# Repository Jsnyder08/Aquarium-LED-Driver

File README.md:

# Reef-LED-Driver
3 Channel LED driver board with PWM fan control <br>
• Utilizes Meanwell LDD-H CC LED Drivers<br>
 Input 9-56 vdc<br>
 1000ma capable output<br>
• Features 3 channel design (Royal Blue, White/Lime, Violet/near IR)<br>
• Utilizes Meanwell SCW 12v DC/DC converter for Fan power<br>
 470ma max output current<br>
• Supports both PWM Fans (4pin) and Standard Fans (3pin)<br>

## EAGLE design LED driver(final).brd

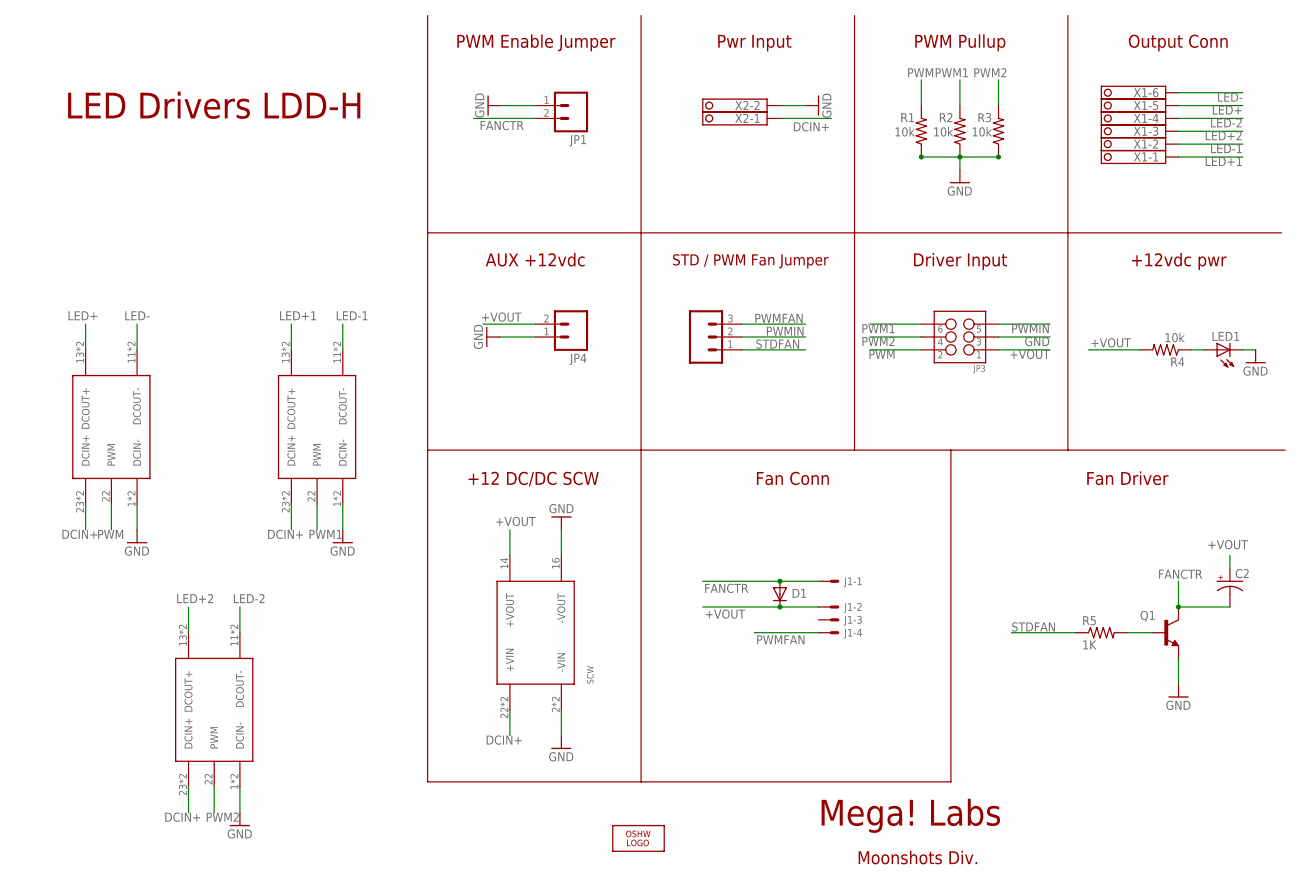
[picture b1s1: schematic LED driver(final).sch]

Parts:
C2: CPOL-USE3.5-8; E3,5-8
D1: CGRM4007-G; SOD-123_MINI-SMA
J1: 22-05-7048-04; 7395-04
JP1: M02LOCK; 1X02_LOCK
JP2: M03LOCK; 1X03_LOCK
JP3: M03X2SHROUD; 2X3-SHROUDED
JP4: M02-JST-2MM-SMT; JST-2-SMD
LED1: LEDCHIPLED_1206; CHIPLED_1206
LOGO2: OSHW_LOGO_6MILX0150-NT; OSHW_6X150_NOTEXT
Q1: BC808-NPN-SOT23-BEC; SOT23-BEC
R1, R2, R3, R4: 10k; M1206
R5: 1K; M1206
U$1, U$2, U$3: LDD_H
U$5: SCW
X1: 1751280
X2: 1751248

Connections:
+VOUT: C2.+, D1.C, J1.2, JP3.1, JP4.2 (1), R4.2, U$5.14 (+VOUT)
C: Q1.B, R5.2
DCIN+: U$1.23 (DCIN+), U$1.24 (DCIN+), U$2.23 (DCIN+), U$2.24 (DCIN+), U$3.23 (DCIN+), U$3.24 (DCIN+), U$5.22 (+VIN), U$5.23 (+VIN), X2.1
FANCTR: C2.-, D1.A, J1.1, JP1.2, Q1.C
GND: JP1.1, JP3.3, JP4.1 (2), LED1.C, Q1.E, R1.1, R2.1, R3.1, U$1.1 (DCIN-), U$1.2 (DCIN-), U$2.1 (DCIN-), U$2.2 (DCIN-), U$3.1 (DCIN-), U$3.2 (DCIN-), U$5.2 (-VIN), U$5.3 (-VIN), U$5.16 (-VOUT), X2.2
LED+: U$1.13 (DCOUT+), U$1.14 (DCOUT+), X1.5
LED+1: U$2.13 (DCOUT+), U$2.14 (DCOUT+), X1.1
LED+2: U$3.13 (DCOUT+), U$3.14 (DCOUT+), X1.3
LED-: U$1.11 (DCOUT-), U$1.12 (DCOUT-), X1.6
LED-1: U$2.11 (DCOUT-), U$2.12 (DCOUT-), X1.2
LED-2: U$3.11 (DCOUT-), U$3.12 (DCOUT-), X1.4
unnamed: LED1.A, R4.1
PWM: JP3.2, R1.2, U$1.22 (PWM)
PWM1: JP3.6, R2.2, U$2.22 (PWM)
PWM2: JP3.4, R3.2, U$3.22 (PWM)
PWMFAN: J1.4, JP2.3
PWMIN: JP2.2, JP3.5
STDFAN: JP2.1, R5.1

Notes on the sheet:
Output Conn
+12vdc pwr
Fan Driver
PWM Pullup
Driver Input
Pwr Input
STD / PWM Fan Jumper
AUX +12vdc
PWM Enable Jumper
Fan Conn
+12 DC/DC SCW
LED Drivers LDD-H
Mega! Labs
Moonshots Div.

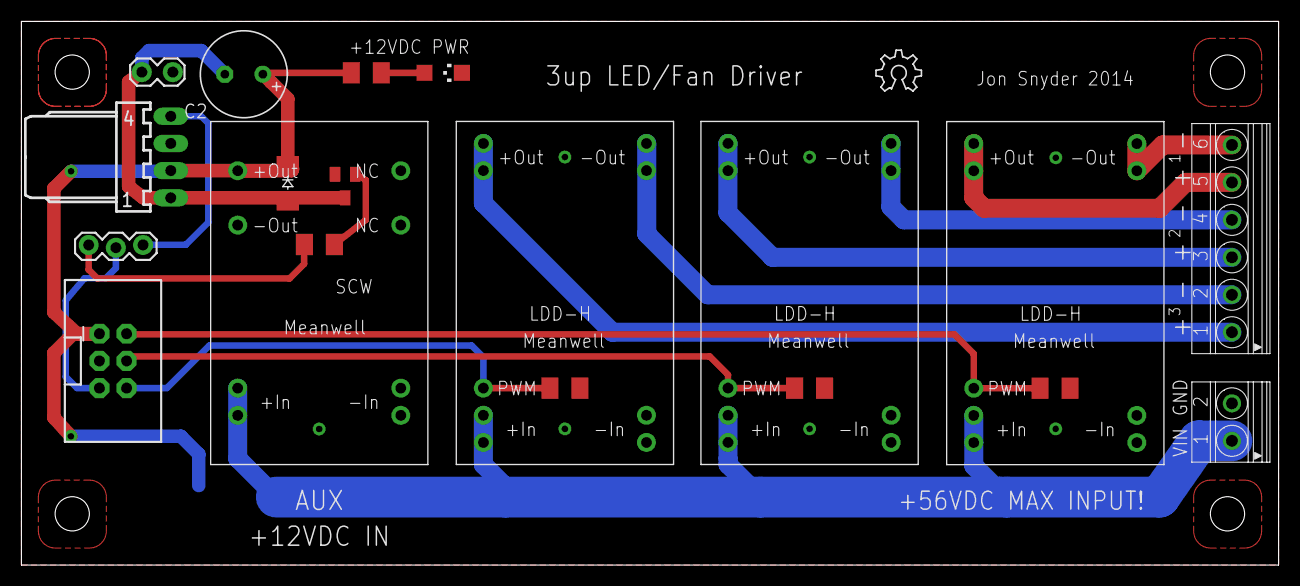
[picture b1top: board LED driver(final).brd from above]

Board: 2 copper layers, 117.5 x 50.8 mm, 21 parts (1 on the bottom side), 18 nets.

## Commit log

2015-11-12 LED Driver

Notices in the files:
parts and their libraries:
SparkFun-Connectors: Licensing: CC v3.0 Share-Alike You are welcome to use this library for commercial purposes.
SparkFun-Aesthetics: Licensing: Creative Commons ShareAlike 4.0 International - https://creativecommons.org/licenses/by-sa/4.0
